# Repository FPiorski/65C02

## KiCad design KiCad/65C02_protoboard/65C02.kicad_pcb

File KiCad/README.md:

# Schematics and PCB layout

### Custom protoboard with two feed-through 2x20pin headers and four power supply lines

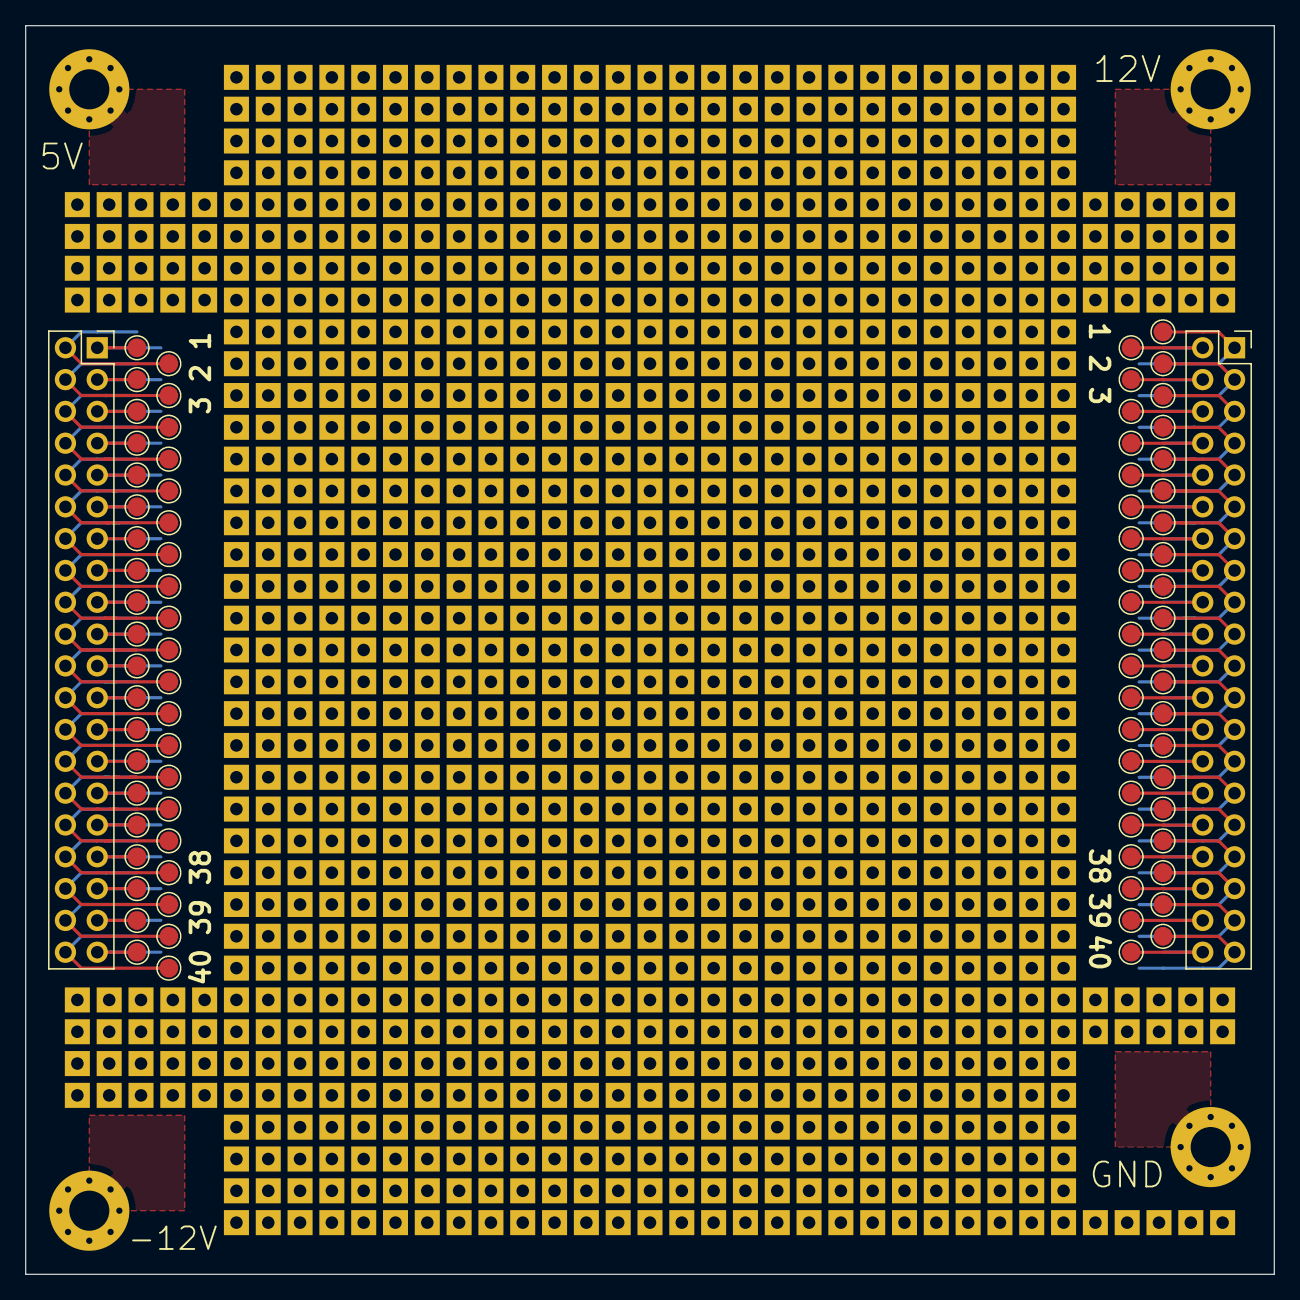
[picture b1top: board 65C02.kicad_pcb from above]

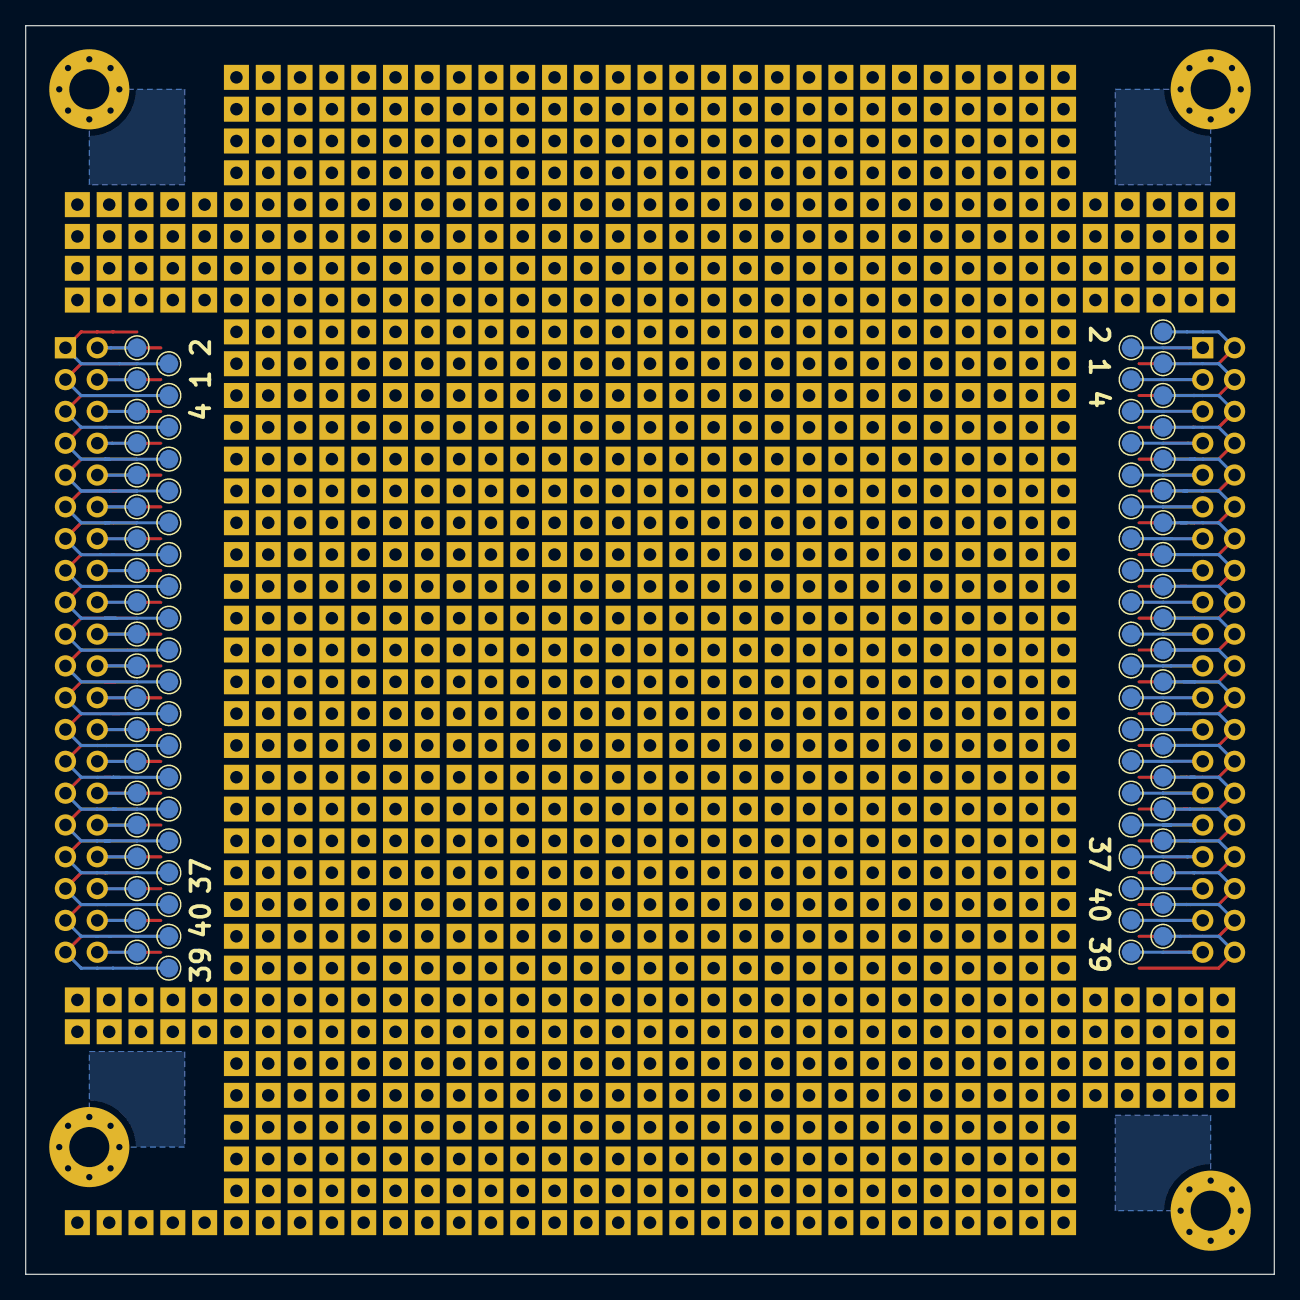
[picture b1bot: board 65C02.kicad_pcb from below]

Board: 2 copper layers, 99.7 x 99.7 mm, 166 parts (80 on the bottom side), 80 nets.

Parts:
5V, 12V: Conn_01x01_Female; MountingHole_3.2mm_M3_Pad_Via
-12V: Conn_01x01_Female; MountingHole_3.2mm_M3_Pad_Via
GND: Conn_01x01_Female; MountingHole_3.2mm_M3_Pad_Via
J5, J6, J7, J8, J9, J10, J11, J12, J13, J14, J15, J16, J17, J18, J19, J20, J21, J22, J23, J24, J25, J26, J27, J28, J29, J30, J31, J32, J33, J34, J35, J36, J37, J38, J39, J40, J41, J42, J43, J44, J45, J46, J47, J48, J49, J50, J51, J52, J53, J54, J55, J56, J57, J58, J59, J60, J61, J62, J63, J64, J65, J66, J67, J68, J69, J70, J71, J72, J73, J74, J75, J76, J77, J78, J79, J80, J81, J82, J83, J84, J87, J88, J89, J90, J91, J92, J93, J94, J95, J96, J97, J98, J99, J100, J101, J102, J103, J104, J105, J106, J107, J108, J109, J110, J111, J112, J113, J114, J115, J116, J117, J118, J119, J120, J121, J122, J123, J124, J125, J126, J127, J128, J129, J130, J131, J132, J133, J134, J135, J136, J137, J138, J139, J140, J141, J142, J143, J144, J145, J146, J147, J148, J149, J150, J151, J152, J153, J154, J155, J156, J157, J158, J159, J160, J161, J162, J163, J164, J165, J166: Conn_01x01_Female; TestPoint_Pad_D1.5mm
Left: Conn_02x20_Odd_Even; PinSocket_2x20_P2.54mm_Vertical
Right: Conn_02x20_Odd_Even; PinSocket_2x20_P2.54mm_Vertical

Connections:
unnamed: J10.1, J50.1, Left.23
unnamed: J11.1, J51.1, Left.27
unnamed: J12.1, J52.1, Left.31
unnamed: J13.1, J53.1, Left.35
unnamed: J14.1, J54.1, Left.39
unnamed: J15.1, J55.1, Right.3
unnamed: J16.1, J56.1, Right.7
unnamed: J17.1, J57.1, Right.11
unnamed: J18.1, J58.1, Right.15
unnamed: J19.1, J59.1, Right.19
unnamed: J20.1, J60.1, Right.23
unnamed: J21.1, J61.1, Right.27
unnamed: J22.1, J62.1, Right.31
unnamed: J23.1, J63.1, Right.35
unnamed: J24.1, J64.1, Right.39
unnamed: J25.1, J65.1, Left.1
unnamed: J26.1, J66.1, Left.5
unnamed: J27.1, J67.1, Left.9
unnamed: J28.1, J68.1, Left.13
unnamed: J29.1, J69.1, Left.17
unnamed: J30.1, J70.1, Left.21
unnamed: J31.1, J71.1, Left.25
unnamed: J32.1, J72.1, Left.29
unnamed: J33.1, J73.1, Left.33
unnamed: J34.1, J74.1, Left.37
unnamed: J35.1, J75.1, Right.1
unnamed: J36.1, J76.1, Right.5
unnamed: J37.1, J77.1, Right.9
unnamed: J38.1, J78.1, Right.13
unnamed: J39.1, J79.1, Right.17
unnamed: J40.1, J80.1, Right.21
unnamed: J41.1, J81.1, Right.25
unnamed: J42.1, J82.1, Right.29
unnamed: J43.1, J83.1, Right.33
unnamed: J44.1, J84.1, Right.37
unnamed: J5.1, J45.1, Left.3
unnamed: J6.1, J46.1, Left.7
unnamed: J7.1, J47.1, Left.11
unnamed: J8.1, J48.1, Left.15
unnamed: J9.1, J49.1, Left.19
unnamed: J100.1, J140.1, Right.14
unnamed: J101.1, J141.1, Right.18
unnamed: J102.1, J142.1, Right.22
unnamed: J103.1, J143.1, Right.26
unnamed: J104.1, J144.1, Right.30
unnamed: J105.1, J145.1, Right.34
unnamed: J106.1, J146.1, Right.38
unnamed: J107.1, J147.1, Left.4
unnamed: J108.1, J148.1, Left.8
unnamed: J109.1, J149.1, Left.12
unnamed: J110.1, J150.1, Left.16
unnamed: J111.1, J151.1, Left.20
unnamed: J112.1, J152.1, Left.24
unnamed: J113.1, J153.1, Left.28
unnamed: J114.1, J154.1, Left.32
unnamed: J115.1, J155.1, Left.36
unnamed: J116.1, J156.1, Left.40
unnamed: J117.1, J157.1, Right.4
unnamed: J118.1, J158.1, Right.8
unnamed: J119.1, J159.1, Right.12
unnamed: J120.1, J160.1, Right.16
unnamed: J121.1, J161.1, Right.20
unnamed: J122.1, J162.1, Right.24
unnamed: J123.1, J163.1, Right.28
unnamed: J124.1, J164.1, Right.32
unnamed: J125.1, J165.1, Right.36
unnamed: J126.1, J166.1, Right.40
unnamed: J87.1, J127.1, Left.2
unnamed: J88.1, J128.1, Left.6
unnamed: J89.1, J129.1, Left.10
unnamed: J90.1, J130.1, Left.14
unnamed: J91.1, J131.1, Left.18
unnamed: J92.1, J132.1, Left.22
unnamed: J93.1, J133.1, Left.26
unnamed: J94.1, J134.1, Left.30
unnamed: J95.1, J135.1, Left.34
unnamed: J96.1, J136.1, Left.38
unnamed: J97.1, J137.1, Right.2
unnamed: J98.1, J138.1, Right.6
unnamed: J99.1, J139.1, Right.10

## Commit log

2019-09-24 Created a KiCad project file
2019-12-27 Protoboard
2020-02-13 Minor git-related changes
2020-02-13 Added the bill of materials
